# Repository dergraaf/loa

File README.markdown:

Project Loa
===========

The goal of the project is to develop a powerfull and flexible control board
for robotic (and other) applications.

A microcontroller from the STM32F series from ST is used as the central
processing unit. It is coupled with a Spartan-3 FPGA from Xilinx which will
be used as a powerfull I/O-Expander. With this combination it is possible to
control multiple motors with encoders and other actuators while processing
sensor data and controlling the robot.

For small robots everything will fit into the control board, for big system
the board can act as combined motor controller and sensor preprocessor.
The actual planning etc. can than be outsourced to a faster microcontroller
or PC connected via USB or a fast UART bus.

Naming
------

A "Loa" is a allknowing ghost in Voodoo. The different boards are named
after loas.

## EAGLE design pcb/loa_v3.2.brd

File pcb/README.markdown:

Documentation
=============

Microcontroller selection
-------------------------

For this controller board we wanted to use a Cortex-M3 chip. There are only two
families in wider use at the moment. The STM32F series from ST and the LPC1700
series from NXP.
One goal was that the microcontroller should be be able to control the drive
system of a robot without the FPGA. Therefore it needs to be able to read
four quadrature encoder and control two motors. This leaves only the STM32
series as the LPC1700 features only one quadrature encoder.

Currently there are four different strains within the STM32 series available.
The STM32F103 was the first one. A lot of development boards use controllers
from this series. But it has a quite long and annoying Errata Sheet, some
peripherals don't work with each other. Most important it is not possible to
use CAN and USB at the same time because they share an internal buffer.
After the 103er the 105/107er arrived. Their most important feature is that it
is possible to use CAN and USB at the same time. Some other stuff like the
ethernet interface are not important for us. The peripherals are improved,
leading to a shorter Errata Sheet. Their only drawback comparted to the 103er
series is that they are limited to 256kB Flash compared to a maximum of
1024kB for the 103er. The 256kB Flash might just be to few for the desired
application as a robot controller.

In the last time two new strains appeared. The STM32F200- and the
STM32F400-series. They are improvments of the 105/107er with a slightly
different pinout. Some of the power pins need to be connected differently, all
of the IO-Pins remain the same. Therefore it is possible to create a board
which supports STM32F1xx and STM32F2xx through some solder jumpers.
The STM32F207 are a bit faster (120MHz instead of 72MHz) and provide more Flash
memory (up to 1024kB). The STM32F407 uses an Cortex-M4 instead of the Cortex-M3
of all the other devices. With 150MHz and an integrated FPU it should be again
faster, especially for floating point calculations. The STM32F4xx are pin
compatible to the STM32F2xx.

As the STM32F4xx are to new and are not yet available from distributors like
Farnell we choose the STM32F207. This leaves the options of an upgrade to a
STM32F407 later.

STM32F207
---------

Pin  | Alternate Functions      | Usage on the Board         | Proposed Usage
---- | ------------------------ | -------------------------- | ----------------
PA0  | ADC0/Timer 2.1/Timer 5.1 |                            | Encoder 1
PA1  | ADC1/Timer 2.2/Timer 5.2 |                            | Encoder 1
PA2  | ADC2/Timer 9.1           |                            |     - 
PA3  | ADC3/Timer 9.2           |                            |     - 
PA4  | SPI1 Cs                  | -> FPGA (DIN)              | 
PA5  | SPI1 Sck                 | -> FPGA                    | 
PA6  | SPI1 Miso                | <- FPGA                    | 
PA7  | SPI1 Mosi                | -> FPGA                    | 
PA8  |                          | <- FPGA                    | 
PA9  | USB Vbus                 | <- USB                     | 
PA10 | USB ID                   | <- USB                     | 
PA11 | USB DM                   | <> USB                     | 
PA12 | USB DP                   | <> USB                     | 
PA13 | TMS                      | <- JTAG                    | 
PA14 | TCK                      | <- JTAG                    | 
PA15 | TDI                      | <- JTAG                    | 
---- | ------------------------ | -------------------------- | ----------------
PB0  | ADC8/Timer 3.3           |                            |     - 
PB1  | ADC9/Timer 3.4           |                            |     - 
PB2  | (BOOT1)                  | FPGA_CCLK                  | 
PB3  | TDO                      | -> JTAG                    | 
PB4  | Timer 3.1/TRST           |                            | Encoder 2
PB5  | Timer 3.2                |                            | Encoder 2
PB6  | UART1 Tx                 |                            | -> Upstream
PB7  | UART1 Rx                 |                            | <- Upstream
PB8  | I2C1 Scl                 |                            |     - 
PB9  | I2C1 Sda                 |                            |     - 
PB10 | I2C2 Scl                 |                            |     - 
PB11 | I2C2 Sda                 |                            |     - 
PB12 | SPI2 Cs /CAN2 Rx         |                            |     - 
PB13 | SPI2 Sck/CAN2 Tx         |                            |     - 
PB14 | SPI2 Miso                |                            |     - 
PB15 | SPI2 Mosi                |                            |     - 
---- | ------------------------ | -------------------------- | ----------------
PC0  | ADC10                    |                            |     - 
PC1  | ADC11                    |                            |     - 
PC2  | ADC12                    |                            |     - 
PC3  | ADC13                    |                            |     - 
PC4  | ADC14                    |                            |     - 
PC5  | ADC15                    |                            |     - 
PC6  | Timer 3.1/Timer 8.1      |                            | Encoder 3
PC7  | Timer 3.2/Timer 8.2      |                            | Encoder 3
PC8  | Timer 3.3/Timer 8.3      |                            |     - 
PC9  | Timer 3.4/Timer 8.4      |                            |     - 
PC10 | UART4 Tx                 |                            | SAB (Sensor Actor Bus)
PC11 | UART4 Rx                 |                            | SAB (       "        )
PC12 | UART5 Tx                 |                            | -> Debug UART
PC13 | (nur als Eingang)        | <- Button 1                | 
PC14 | (nur als Eingang)        | <- FPGA (DONE)             | 
PC15 | (nur als Eingang)        | <- SD Card Detect          | 
---- | ------------------------ | -------------------------- | ----------------
PD0  | CAN1 Rx                  | <- CAN                     | 
PD1  | CAN1 Tx                  | -> CAN                     | 
PD2  | UART5 Rx                 |                            | <- Debug UART
PD3  |                          | -> SD Card (CS)            | 
PD4  |                          |                            |     - 
PD5  | UART2 Tx                 |                            | SPI 1
PD6  | UART2 Rx                 |                            | SPI 1
PD7  | UART2 Ck                 |                            | SPI 1
PD8  | UART3 Tx                 | -> SD Card/Dataflash       | 
PD9  | UART3 Rx                 | <- SD Card/Dataflash       | 
PD10 | UART3 Ck                 | -> SD Card/Dataflash       | 
PD11 |                          | -> Dataflash (CS)          | 
PD12 | Timer 4.1                |                            | Encoder 4
PD13 | Timer 4.2                |                            | Encoder 4
PD14 | Timer 4.3                |                            |     - 
PD15 | Timer 4.4                |                            |     - 
---- | ------------------------ | -------------------------- | ----------------
PE0  |                          | -> FPGA (CCLK)             | 
PE1  |                          | -> FPGA (PROG_B)           | 
PE2  |                          | -> FPGA                    | 
PE3  |                          | -> LED0                    | 
PE4  |                          | -> LED1                    | 
PE5  | Timer 9.1                | -> LED2                    | 
PE6  | Timer 9.2                | -> LED3                    | 
PE7  |                          | <- FPGA (INIT_B)           | 
PE8  | Timer 1.1N               |                            | Motor 1
PE9  | Timer 1.1                |                            | Motor 1
PE10 | Timer 1.2N               |                            | Motor 2
PE11 | Timer 1.2                |                            | Motor 2
PE12 | Timer 1.3N               |                            |     - 
PE13 | Timer 1.3                |                            |     - 
PE14 | Timer 1.4                |                            |     - 
PE15 |                          |                            |     - 

#### Peripherals

- 2x Motor (Timer 1)
- 4x Encoder (Timer 3+4+5+8)

- 1x Upstream (Uart 1)
- 1x Debug (Uart 5)
- 2x SPI (Uart2+SPI2)
- 1x Peripheral UART (Uart 4)

#### SPI vs. SDIO

We choose a SPI over the SDIO interface for the SD Card because SDIO would
have blocked UART4 and UART5.

#### JTAG Connector

This is the official JTAG Connector proposed by ARM for the Cortex-M3. The only
difference is that we don't use a 1.27mm grid but a normal 2.54mm one. This
allows to use standard ribbon cable.

            ------
    3.3V --| 1  2 |-- TMS
     GND --| 3  4 |-- TCLK
     GND -[| 5  6 |-- TDO
    RTCK --| 7  8 |-- TDI
     GND --| 9 10 |-- Reset (SRST)
            ------

On this connector TRST (also called NJTRST) is not connected. This might
lead to the problem that the "reset halt" command from OpenOCD doesn't work.

RTCK is only used for ARM7 devices, so it is left open here.

FPGA Spartan-3
--------------

The Spartan-3 was choosen because it was the only FPGA from all the Spartan-3
Series (3,3E,3A,3AN) that is available in TQFP144 package from Reichelt or
Farnell.

The XC3S50A and XC3S50AN are also available, but the bigger packages are not.

### Pins

Unused pins are defined as inputs with pull-downs by default. Can be changed
by primitives or constraints in the bitstream generation.

All user-I/O pins, input-only pins, and dual-purpose pins that are not actively
involved in the currently-selected configuration mode are high impedance
(floating, three-stated, Hi-Z) during the configuration process.

### Configuration of the FPGA

DONE
:   Output with 2,5V supply. Driven low during configuration. Goes high after
    configuration has finished.

PROG_B
:   Input with 2,5 supply. Low pulse (>= 500ns) restarts the configuration
    process.

CCLK
:   Input with 2,5 supply in slave modes. Configuration clock.

DIN
:   Serial Mode input

DOUT
:   Serial Data Output. Not used in single FPGA designs.

INIT_B
:   Output with 3,3V supply. Driven low during before configuration. After it
    goes high the M[2:0] pins are sampled and the configuration is started.
    Holding the pin low stalls the configuration start. During configuration
    the FPGA indicates the occurrence of a configuration
    data error (i.e., CRC error) by asserting INIT_B Low.
    After configuration successfully completes, i.e., when the DONE pin goes
    High, the INIT_B pin is available as a full user-I/O pin.

HSWAP_EN 
:   When the pin is Low, each pin (not only the configuration pins) has an
    internal pull-up resistor that is active throughout configuration, starting
    immediately on power-up.

M[2:0]
:   Select the configuration mode.
    '111' Slave Serial Mode
    '101' JTAG Mode

#### Spartan 3 Bitstream Size

Device  | Configuration
        |  Size [Bits]
------- | --------------
XC3S50  |     439,264
XC3S200 |   1,047,616
XC3S400 |   1,699,136

### Power Supply

http://focus.ti.com/analog/docs/refdesignovw.tsp?familyId=64&contentType=2&genContentId=34823

For the XC3S250E:
- 1.2V at 1A
- 2.5V at 0.15A
- 3.3V at 3A

For the XC3S500E
- 1.2V at 1.5A
- 2.5V at 0.15A
- 3.3V at 3A

The XC3S200/400 should be somewhere in between, the XC3S50 significantly lower.

### JTAG Connector

The JTAG connector is a stripped down version of the original connector from
the Xilinx Parallel Cable IV. Original it uses 14 pins, but we leave the last
four pins out to fit it to a standard 10 pin header. These pins are only used
for programming the FPGA via Slave Serial mode through the PC so no
functionality is lost.

           ------
    GND --| 1  2 |-- Vref (connect to Vaux)
    GND --| 3  4 |-- TMS
    GND -[| 5  6 |-- TCK
    GND --| 7  8 |-- TDO
    GND --| 9 10 |-- TDI
           ------

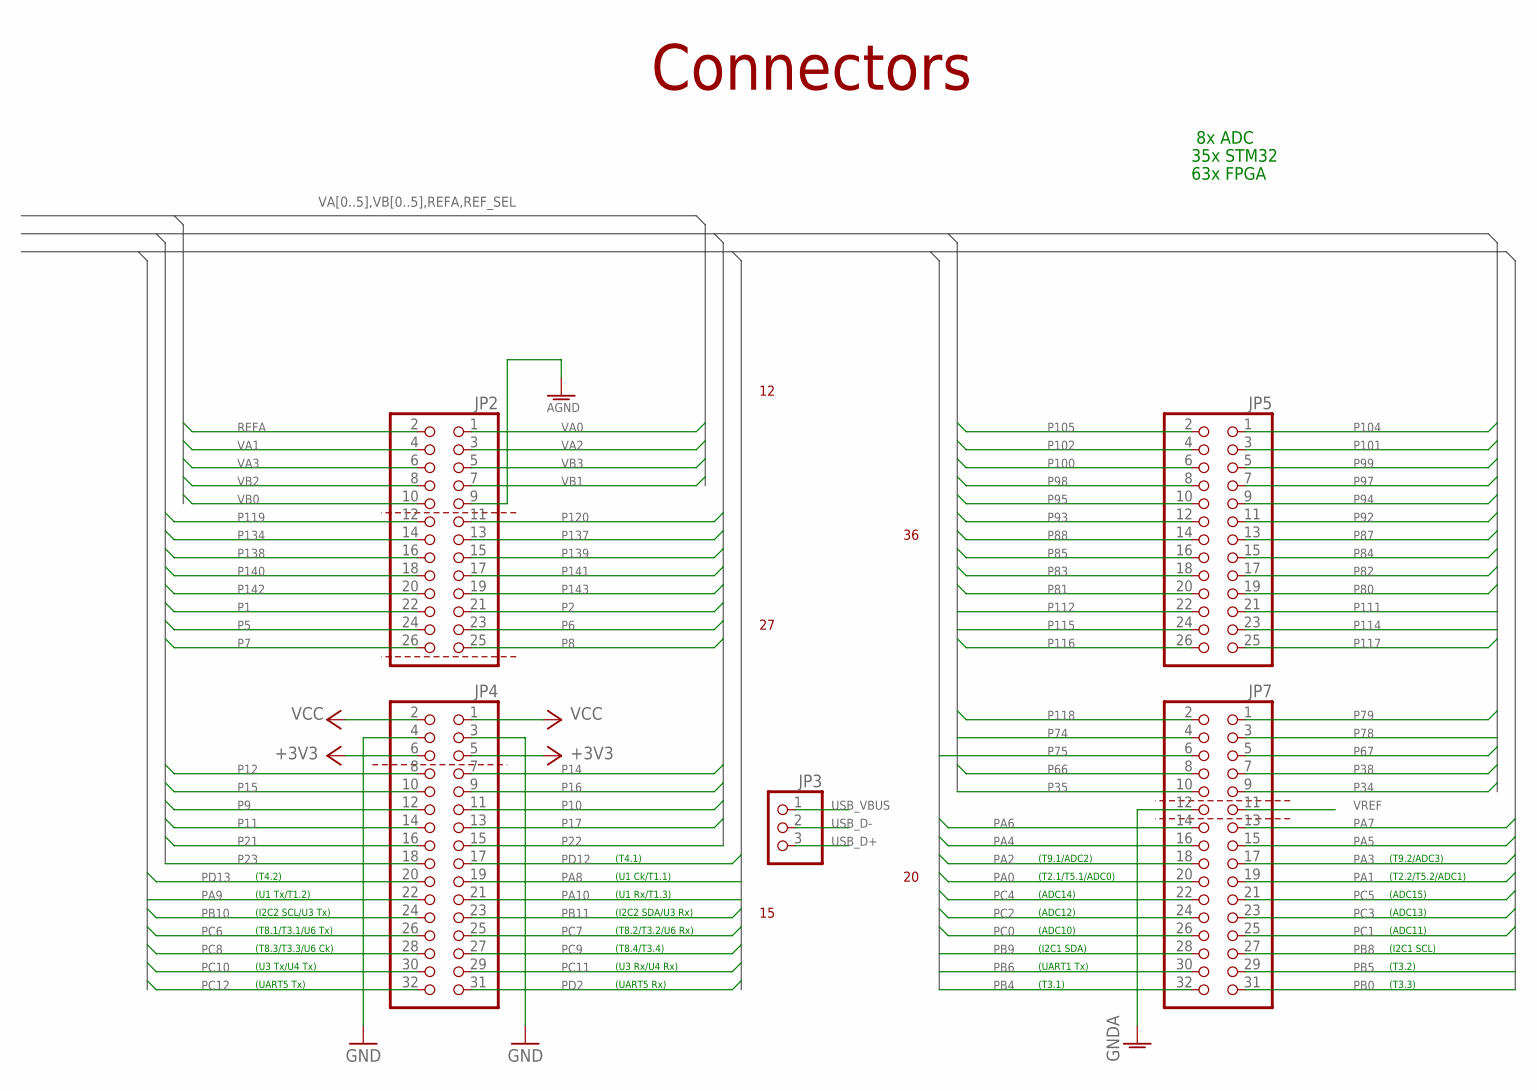
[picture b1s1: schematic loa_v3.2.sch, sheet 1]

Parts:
JP2, JP5: PINHD-2X13_2.54-SMD; 2X13SMD
JP3: PINHD-1X3_2.54S; 1X03S
JP4, JP7: PINHD-2X16_2.54-SMD; 2X16SMD

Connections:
+3V3: JP4.5, JP4.6; also elsewhere on the board
AGND: JP2.9; also elsewhere on the board
GND: JP4.3, JP4.4; also elsewhere on the board
GNDA: JP7.12; also elsewhere on the board
P1: JP2.22; also elsewhere on the board
P2: JP2.21; also elsewhere on the board
P5: JP2.24; also elsewhere on the board
P6: JP2.23; also elsewhere on the board
P7: JP2.26; also elsewhere on the board
P8: JP2.25; also elsewhere on the board
P9: JP4.12; also elsewhere on the board
P10: JP4.11; also elsewhere on the board
P11: JP4.14; also elsewhere on the board
P12: JP4.8; also elsewhere on the board
P14: JP4.7; also elsewhere on the board
P15: JP4.10; also elsewhere on the board
P16: JP4.9; also elsewhere on the board
P17: JP4.13; also elsewhere on the board
P21: JP4.16; also elsewhere on the board
P22: JP4.15; also elsewhere on the board
P23: JP4.18; also elsewhere on the board
P34: JP7.9; also elsewhere on the board
P35: JP7.10; also elsewhere on the board
P38: JP7.7; also elsewhere on the board
P66: JP7.8; also elsewhere on the board
P67: JP7.5; also elsewhere on the board
P74: JP7.4; also elsewhere on the board
P75: JP7.6; also elsewhere on the board
P78: JP7.3; also elsewhere on the board
P79: JP7.1; also elsewhere on the board
P80: JP5.19; also elsewhere on the board
P81: JP5.20; also elsewhere on the board
P82: JP5.17; also elsewhere on the board
P83: JP5.18; also elsewhere on the board
P84: JP5.15; also elsewhere on the board
P85: JP5.16; also elsewhere on the board
P87: JP5.13; also elsewhere on the board
P88: JP5.14; also elsewhere on the board
P92: JP5.11; also elsewhere on the board
P93: JP5.12; also elsewhere on the board
P94: JP5.9; also elsewhere on the board
P95: JP5.10; also elsewhere on the board
P97: JP5.7; also elsewhere on the board
P98: JP5.8; also elsewhere on the board
P99: JP5.5; also elsewhere on the board
P100: JP5.6; also elsewhere on the board
P101: JP5.3; also elsewhere on the board
P102: JP5.4; also elsewhere on the board
P104: JP5.1; also elsewhere on the board
P105: JP5.2; also elsewhere on the board
P111: JP5.21; also elsewhere on the board
P112: JP5.22; also elsewhere on the board
P114: JP5.23; also elsewhere on the board
P115: JP5.24; also elsewhere on the board
P116: JP5.26; also elsewhere on the board
P117: JP5.25; also elsewhere on the board
P118: JP7.2; also elsewhere on the board
P119: JP2.12; also elsewhere on the board
P120: JP2.11; also elsewhere on the board
P134: JP2.14; also elsewhere on the board
P137: JP2.13; also elsewhere on the board
P138: JP2.16; also elsewhere on the board
P139: JP2.15; also elsewhere on the board
P140: JP2.18; also elsewhere on the board
P141: JP2.17; also elsewhere on the board
P142: JP2.20; also elsewhere on the board
P143: JP2.19; also elsewhere on the board
PA0: JP7.20; also elsewhere on the board
PA1: JP7.19; also elsewhere on the board
PA2: JP7.18; also elsewhere on the board
PA3: JP7.17; also elsewhere on the board
PA4: JP7.16; also elsewhere on the board
PA5: JP7.15; also elsewhere on the board
PA6: JP7.14; also elsewhere on the board
PA7: JP7.13; also elsewhere on the board
PA8: JP4.19; also elsewhere on the board
PA9: JP4.22; also elsewhere on the board
PA10: JP4.21; also elsewhere on the board
PB0: JP7.31; also elsewhere on the board
PB4: JP7.32; also elsewhere on the board
PB5: JP7.29; also elsewhere on the board
PB6: JP7.30; also elsewhere on the board
PB8: JP7.27; also elsewhere on the board
PB9: JP7.28; also elsewhere on the board
PB10: JP4.24; also elsewhere on the board
PB11: JP4.23; also elsewhere on the board
PC0: JP7.26; also elsewhere on the board
PC1: JP7.25; also elsewhere on the board
PC2: JP7.24; also elsewhere on the board
PC3: JP7.23; also elsewhere on the board
PC4: JP7.22; also elsewhere on the board
PC5: JP7.21; also elsewhere on the board
PC6: JP4.26; also elsewhere on the board
PC7: JP4.25; also elsewhere on the board
PC8: JP4.28; also elsewhere on the board
PC9: JP4.27; also elsewhere on the board
PC10: JP4.30; also elsewhere on the board
PC11: JP4.29; also elsewhere on the board
PC12: JP4.32; also elsewhere on the board
PD2: JP4.31; also elsewhere on the board
PD12: JP4.17; also elsewhere on the board
PD13: JP4.20; also elsewhere on the board
REFA: JP2.2; also elsewhere on the board
USB_D+: JP3.3; also elsewhere on the board
USB_D-: JP3.2; also elsewhere on the board
USB_VBUS: JP3.1; also elsewhere on the board
VA0: JP2.1; also elsewhere on the board
VA1: JP2.4; also elsewhere on the board
VA2: JP2.3; also elsewhere on the board
VA3: JP2.6; also elsewhere on the board
VB0: JP2.10; also elsewhere on the board
VB1: JP2.7; also elsewhere on the board
VB2: JP2.8; also elsewhere on the board
VB3: JP2.5; also elsewhere on the board
VCC: JP4.1, JP4.2; also elsewhere on the board
VREF: JP7.11; also elsewhere on the board

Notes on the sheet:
Connectors
(T2.1/T5.1/ADC0)
(T2.2/T5.2/ADC1)
(T9.1/ADC2)
(T9.2/ADC3)
(ADC10)
(ADC11)
(ADC12)
(ADC13)
(ADC14)
(ADC15)
(I2C1 SCL)
(I2C1 SDA)
(UART1 Tx)
(T3.1)
(T3.2)
(UART5 Rx)
(UART5 Tx)
(T8.1/T3.1/U6 Tx)
(T8.2/T3.2/U6 Rx)
(T8.3/T3.3/U6 Ck)
(T8.4/T3.4)
(T4.2)
(T4.1)
(U1 Tx/T1.2)
(U1 Rx/T1.3)
(U1 Ck/T1.1)
(U3 Tx/U4 Tx)
(U3 Rx/U4 Rx)
(I2C2 SDA/U3 Rx)
(I2C2 SCL/U3 Tx)
8x ADC
35x STM32
63x FPGA
(T3.3)

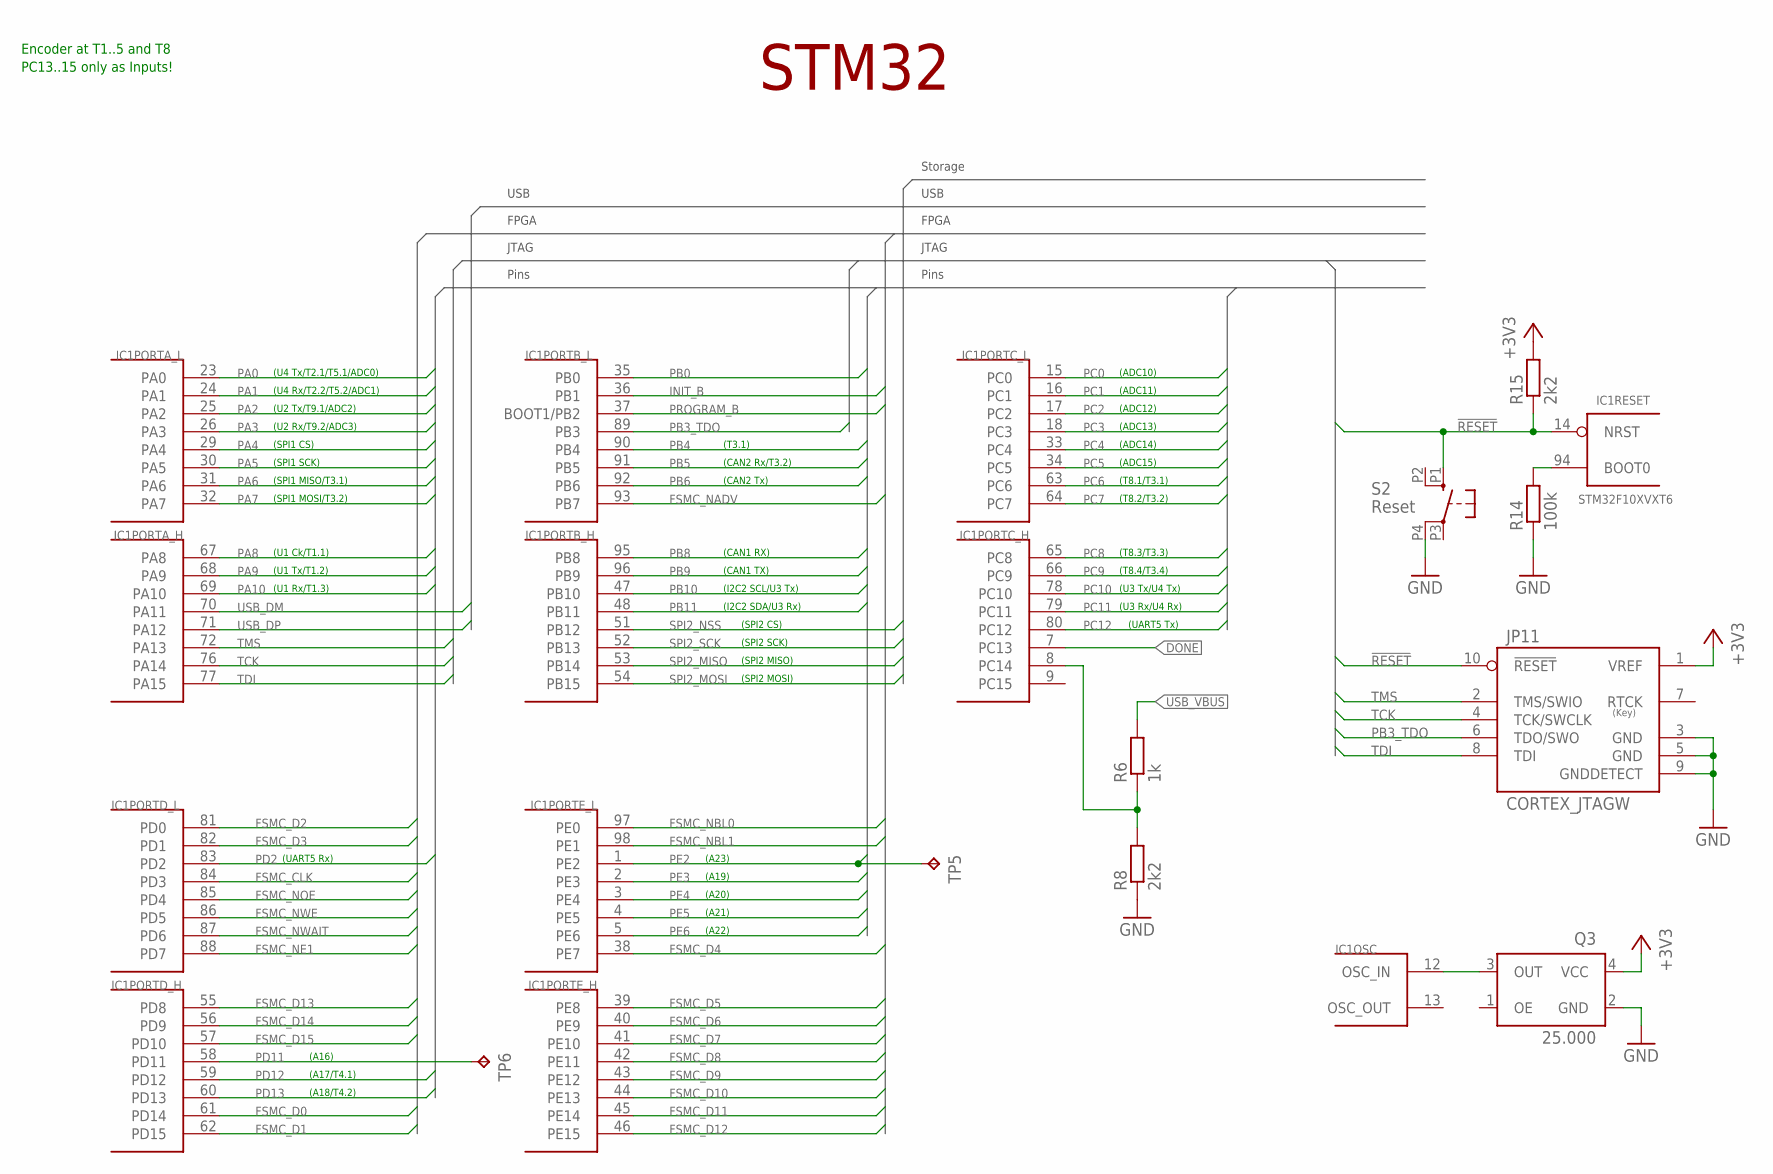
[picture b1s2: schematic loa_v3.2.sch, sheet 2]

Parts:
IC1: STM32F10XVXT6; TQFP100; DIGIKEY# 497-11605-ND
JP11: CORTEX_JTAGW; ML10
Q3: 25.000; XO53
R6: 1k; R0603
R8, R15: 2k2; R0603
R14: 100k; R0603
S2: Reset; B3F-10XX-SMD
TP5, TP6: TPB1,27; B1,27

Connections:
!RESET: IC1.14 (NRST), JP11.10 (!RESET), R15.1, S2.P1 (S)
+3V3: JP11.1 (VREF), Q3.4 (VCC), R15.2; also elsewhere on the board
DONE: IC1.7 (PC13); also elsewhere on the board
FSMC_CLK: IC1.84 (PD3); also elsewhere on the board
FSMC_D0: IC1.61 (PD14); also elsewhere on the board
FSMC_D1: IC1.62 (PD15); also elsewhere on the board
FSMC_D2: IC1.81 (PD0); also elsewhere on the board
FSMC_D3: IC1.82 (PD1); also elsewhere on the board
FSMC_D4: IC1.38 (PE7); also elsewhere on the board
FSMC_D5: IC1.39 (PE8); also elsewhere on the board
FSMC_D6: IC1.40 (PE9); also elsewhere on the board
FSMC_D7: IC1.41 (PE10); also elsewhere on the board
FSMC_D8: IC1.42 (PE11); also elsewhere on the board
FSMC_D9: IC1.43 (PE12); also elsewhere on the board
FSMC_D10: IC1.44 (PE13); also elsewhere on the board
FSMC_D11: IC1.45 (PE14); also elsewhere on the board
FSMC_D12: IC1.46 (PE15); also elsewhere on the board
FSMC_D13: IC1.55 (PD8); also elsewhere on the board
FSMC_D14: IC1.56 (PD9); also elsewhere on the board
FSMC_D15: IC1.57 (PD10); also elsewhere on the board
FSMC_NADV: IC1.93 (PB7); also elsewhere on the board
FSMC_NBL0: IC1.97 (PE0); also elsewhere on the board
FSMC_NBL1: IC1.98 (PE1); also elsewhere on the board
FSMC_NE1: IC1.88 (PD7); also elsewhere on the board
FSMC_NOE: IC1.85 (PD4); also elsewhere on the board
FSMC_NWAIT: IC1.87 (PD6); also elsewhere on the board
FSMC_NWE: IC1.86 (PD5); also elsewhere on the board
GND: JP11.3 (GND), JP11.5 (GND), JP11.9 (GNDDETECT), Q3.2 (GND), R8.1, R14.1, S2.P4 (P1); also elsewhere on the board
INIT_B: IC1.36 (PB1); also elsewhere on the board
unnamed: IC1.8 (PC14), R6.1, R8.2
unnamed: IC1.94 (BOOT0), R14.2
unnamed: IC1.12 (OSC_IN), Q3.3 (OUT)
PA0: IC1.23 (PA0); also elsewhere on the board
PA1: IC1.24 (PA1); also elsewhere on the board
PA2: IC1.25 (PA2); also elsewhere on the board
PA3: IC1.26 (PA3); also elsewhere on the board
PA4: IC1.29 (PA4); also elsewhere on the board
PA5: IC1.30 (PA5); also elsewhere on the board
PA6: IC1.31 (PA6); also elsewhere on the board
PA7: IC1.32 (PA7); also elsewhere on the board
PA8: IC1.67 (PA8); also elsewhere on the board
PA9: IC1.68 (PA9); also elsewhere on the board
PA10: IC1.69 (PA10); also elsewhere on the board
PB0: IC1.35 (PB0); also elsewhere on the board
PB3_TDO: IC1.89 (PB3), JP11.6 (TDO/SWO)
PB4: IC1.90 (PB4); also elsewhere on the board
PB5: IC1.91 (PB5); also elsewhere on the board
PB6: IC1.92 (PB6); also elsewhere on the board
PB8: IC1.95 (PB8); also elsewhere on the board
PB9: IC1.96 (PB9); also elsewhere on the board
PB10: IC1.47 (PB10); also elsewhere on the board
PB11: IC1.48 (PB11); also elsewhere on the board
PC0: IC1.15 (PC0); also elsewhere on the board
PC1: IC1.16 (PC1); also elsewhere on the board
PC2: IC1.17 (PC2); also elsewhere on the board
PC3: IC1.18 (PC3); also elsewhere on the board
PC4: IC1.33 (PC4); also elsewhere on the board
PC5: IC1.34 (PC5); also elsewhere on the board
PC6: IC1.63 (PC6); also elsewhere on the board
PC7: IC1.64 (PC7); also elsewhere on the board
PC8: IC1.65 (PC8); also elsewhere on the board
PC9: IC1.66 (PC9); also elsewhere on the board
PC10: IC1.78 (PC10); also elsewhere on the board
PC11: IC1.79 (PC11); also elsewhere on the board
PC12: IC1.80 (PC12); also elsewhere on the board
PD2: IC1.83 (PD2); also elsewhere on the board
PD11: IC1.58 (PD11), TP6.TP
PD12: IC1.59 (PD12); also elsewhere on the board
PD13: IC1.60 (PD13); also elsewhere on the board
PE2: IC1.1 (PE2), TP5.TP
PE3: IC1.2 (PE3); also elsewhere on the board
PE4: IC1.3 (PE4); also elsewhere on the board
PE5: IC1.4 (PE5); also elsewhere on the board
PE6: IC1.5 (PE6); also elsewhere on the board
PROGRAM_B: IC1.37 (BOOT1/PB2); also elsewhere on the board
SPI2_MISO: IC1.53 (PB14); also elsewhere on the board
SPI2_MOSI: IC1.54 (PB15); also elsewhere on the board
SPI2_NSS: IC1.51 (PB12); also elsewhere on the board
SPI2_SCK: IC1.52 (PB13); also elsewhere on the board
TCK: IC1.76 (PA14), JP11.4 (TCK/SWCLK)
TDI: IC1.77 (PA15), JP11.8 (TDI)
TMS: IC1.72 (PA13), JP11.2 (TMS/SWIO)
USB_DM: IC1.70 (PA11); also elsewhere on the board
USB_DP: IC1.71 (PA12); also elsewhere on the board
USB_VBUS: R6.2; also elsewhere on the board

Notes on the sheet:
(U4 Tx/T2.1/T5.1/ADC0)
(U4 Rx/T2.2/T5.2/ADC1)
(U2 Tx/T9.1/ADC2)
(U2 Rx/T9.2/ADC3)
(T3.1)
(CAN2 Rx/T3.2)
(CAN1 RX)
(CAN1 TX)
(I2C2 SDA/U3 Rx)
(I2C2 SCL/U3 Tx)
(CAN2 Tx)
(U3 Tx/U4 Tx)
(U3 Rx/U4 Rx)
(UART5 Rx)
STM32
Encoder at T1..5 and T8
(ADC10)
(ADC11)
(ADC12)
(ADC13)
(ADC14)
(ADC15)
(T8.1/T3.1)
(T8.2/T3.2)
(T8.3/T3.3)
(T8.4/T3.4)
PC13..15 only as Inputs!
(UART5 Tx)
(A18/T4.2)
(A17/T4.1)
(A16)
(A23)
(A19)
(A20)
(A21)
(A22)
(U1 Tx/T1.2)
(U1 Rx/T1.3)
(SPI1 CS)
(SPI1 SCK)

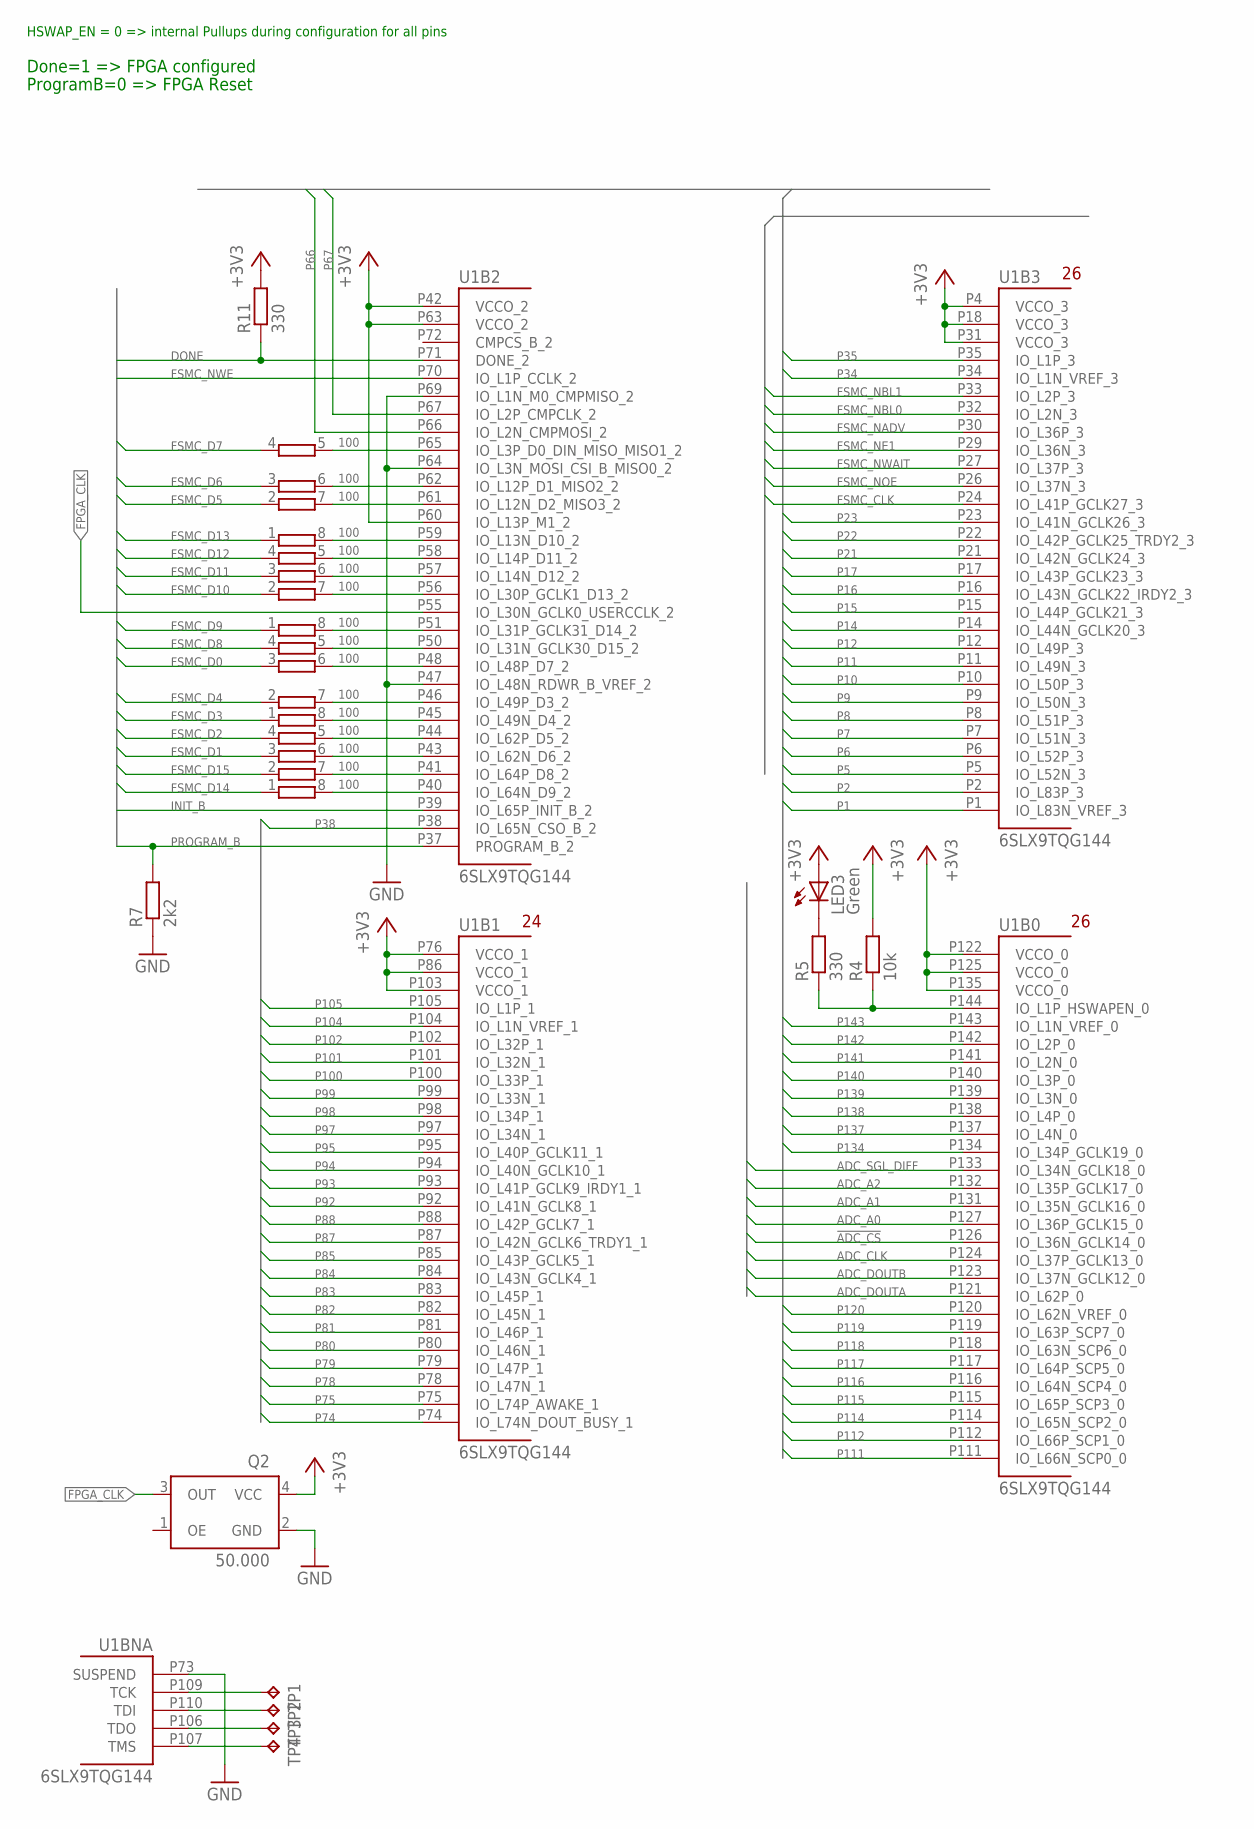
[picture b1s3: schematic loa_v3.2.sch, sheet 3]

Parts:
LED3: Green; CHIPLED_0805
Q2: 50.000; XO53
R4: 10k; R0603
R5, R11: 330; R0603
R7: 2k2; R0805
RN3, RN4, RN6, RN7: 100; EXB38V
TP1, TP2, TP3, TP4: TPB1,27; B1,27
U1: 6SLX9TQG144; TQ144; DIGIKEY# 122-1745-ND

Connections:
!ADC_CS: U1.P126 (IO_L36N_GCLK14_0); also elsewhere on the board
+3V3: LED3.A, Q2.4 (VCC), R4.2, R11.2, U1.P4 (VCCO_3), U1.P18 (VCCO_3), U1.P31 (VCCO_3), U1.P42 (VCCO_2), U1.P60 (IO_L13P_M1_2), U1.P63 (VCCO_2), U1.P76 (VCCO_1), U1.P86 (VCCO_1), U1.P103 (VCCO_1), U1.P122 (VCCO_0), U1.P125 (VCCO_0), U1.P135 (VCCO_0); also elsewhere on the board
ADC_A0: U1.P127 (IO_L36P_GCLK15_0); also elsewhere on the board
ADC_A1: U1.P131 (IO_L35N_GCLK16_0); also elsewhere on the board
ADC_A2: U1.P132 (IO_L35P_GCLK17_0); also elsewhere on the board
ADC_CLK: U1.P124 (IO_L37P_GCLK13_0); also elsewhere on the board
ADC_DOUTA: U1.P121 (IO_L62P_0); also elsewhere on the board
ADC_DOUTB: U1.P123 (IO_L37N_GCLK12_0); also elsewhere on the board
ADC_SGL_DIFF: U1.P133 (IO_L34N_GCLK18_0); also elsewhere on the board
DONE: R11.1, U1.P71 (DONE_2); also elsewhere on the board
FPGA_CLK: Q2.3 (OUT), U1.P55 (IO_L30N_GCLK0_USERCCLK_2)
FPGA_TCK: TP1.TP, U1.P109 (TCK)
FPGA_TDI: TP2.TP, U1.P110 (TDI)
FPGA_TDO: TP3.TP, U1.P106 (TDO)
FPGA_TMS: TP4.TP, U1.P107 (TMS)
FSMC_CLK: U1.P24 (IO_L41P_GCLK27_3); also elsewhere on the board
FSMC_D0: RN7.3 (1); also elsewhere on the board
FSMC_D1: RN4.3 (1); also elsewhere on the board
FSMC_D2: RN4.4 (1); also elsewhere on the board
FSMC_D3: RN7.1; also elsewhere on the board
FSMC_D4: RN7.2 (1); also elsewhere on the board
FSMC_D5: RN3.2 (1); also elsewhere on the board
FSMC_D6: RN3.3 (1); also elsewhere on the board
FSMC_D7: RN3.4 (1); also elsewhere on the board
FSMC_D8: RN7.4 (1); also elsewhere on the board
FSMC_D9: RN6.1; also elsewhere on the board
FSMC_D10: RN6.2 (1); also elsewhere on the board
FSMC_D11: RN6.3 (1); also elsewhere on the board
FSMC_D12: RN6.4 (1); also elsewhere on the board
FSMC_D13: RN3.1; also elsewhere on the board
FSMC_D14: RN4.1; also elsewhere on the board
FSMC_D15: RN4.2 (1); also elsewhere on the board
FSMC_NADV: U1.P30 (IO_L36P_3); also elsewhere on the board
FSMC_NBL0: U1.P32 (IO_L2N_3); also elsewhere on the board
FSMC_NBL1: U1.P33 (IO_L2P_3); also elsewhere on the board
FSMC_NE1: U1.P29 (IO_L36N_3); also elsewhere on the board
FSMC_NOE: U1.P26 (IO_L37N_3); also elsewhere on the board
FSMC_NWAIT: U1.P27 (IO_L37P_3); also elsewhere on the board
FSMC_NWE: U1.P70 (IO_L1P_CCLK_2); also elsewhere on the board
GND: Q2.2 (GND), R7.1, U1.P47 (IO_L48N_RDWR_B_VREF_2), U1.P64 (IO_L3N_MOSI_CSI_B_MISO0_2), U1.P69 (IO_L1N_M0_CMPMISO_2), U1.P73 (SUSPEND); also elsewhere on the board
INIT_B: U1.P39 (IO_L65P_INIT_B_2); also elsewhere on the board
unnamed: RN3.5 (2), U1.P65 (IO_L3P_D0_DIN_MISO_MISO1_2)
unnamed: RN3.6 (2), U1.P62 (IO_L12P_D1_MISO2_2)
unnamed: RN3.7 (2), U1.P61 (IO_L12N_D2_MISO3_2)
unnamed: RN3.8 (2), U1.P59 (IO_L13N_D10_2)
unnamed: RN6.5 (2), U1.P58 (IO_L14P_D11_2)
unnamed: RN6.6 (2), U1.P57 (IO_L14N_D12_2)
unnamed: RN6.7 (2), U1.P56 (IO_L30P_GCLK1_D13_2)
unnamed: RN6.8 (2), U1.P51 (IO_L31P_GCLK31_D14_2)
unnamed: RN7.5 (2), U1.P50 (IO_L31N_GCLK30_D15_2)
unnamed: RN7.6 (2), U1.P48 (IO_L48P_D7_2)
unnamed: RN7.7 (2), U1.P46 (IO_L49P_D3_2)
unnamed: RN7.8 (2), U1.P45 (IO_L49N_D4_2)
unnamed: RN4.5 (2), U1.P44 (IO_L62P_D5_2)
unnamed: LED3.C, R5.2
unnamed: R4.1, R5.1, U1.P144 (IO_L1P_HSWAPEN_0)
unnamed: RN4.7 (2), U1.P41 (IO_L64P_D8_2)
unnamed: RN4.6 (2), U1.P43 (IO_L62N_D6_2)
unnamed: RN4.8 (2), U1.P40 (IO_L64N_D9_2)
P1: U1.P1 (IO_L83N_VREF_3); also elsewhere on the board
P2: U1.P2 (IO_L83P_3); also elsewhere on the board
P5: U1.P5 (IO_L52N_3); also elsewhere on the board
P6: U1.P6 (IO_L52P_3); also elsewhere on the board
P7: U1.P7 (IO_L51N_3); also elsewhere on the board
P8: U1.P8 (IO_L51P_3); also elsewhere on the board
P9: U1.P9 (IO_L50N_3); also elsewhere on the board
P10: U1.P10 (IO_L50P_3); also elsewhere on the board
P11: U1.P11 (IO_L49N_3); also elsewhere on the board
P12: U1.P12 (IO_L49P_3); also elsewhere on the board
P14: U1.P14 (IO_L44N_GCLK20_3); also elsewhere on the board
P15: U1.P15 (IO_L44P_GCLK21_3); also elsewhere on the board
P16: U1.P16 (IO_L43N_GCLK22_IRDY2_3); also elsewhere on the board
P17: U1.P17 (IO_L43P_GCLK23_3); also elsewhere on the board
P21: U1.P21 (IO_L42N_GCLK24_3); also elsewhere on the board
P22: U1.P22 (IO_L42P_GCLK25_TRDY2_3); also elsewhere on the board
P23: U1.P23 (IO_L41N_GCLK26_3); also elsewhere on the board
P34: U1.P34 (IO_L1N_VREF_3); also elsewhere on the board
P35: U1.P35 (IO_L1P_3); also elsewhere on the board
P38: U1.P38 (IO_L65N_CSO_B_2); also elsewhere on the board
P66: U1.P66 (IO_L2N_CMPMOSI_2); also elsewhere on the board
P67: U1.P67 (IO_L2P_CMPCLK_2); also elsewhere on the board
P74: U1.P74 (IO_L74N_DOUT_BUSY_1); also elsewhere on the board
P75: U1.P75 (IO_L74P_AWAKE_1); also elsewhere on the board
P78: U1.P78 (IO_L47N_1); also elsewhere on the board
P79: U1.P79 (IO_L47P_1); also elsewhere on the board
P80: U1.P80 (IO_L46N_1); also elsewhere on the board
P81: U1.P81 (IO_L46P_1); also elsewhere on the board
P82: U1.P82 (IO_L45N_1); also elsewhere on the board
P83: U1.P83 (IO_L45P_1); also elsewhere on the board
P84: U1.P84 (IO_L43N_GCLK4_1); also elsewhere on the board
P85: U1.P85 (IO_L43P_GCLK5_1); also elsewhere on the board
P87: U1.P87 (IO_L42N_GCLK6_TRDY1_1); also elsewhere on the board
P88: U1.P88 (IO_L42P_GCLK7_1); also elsewhere on the board
P92: U1.P92 (IO_L41N_GCLK8_1); also elsewhere on the board
P93: U1.P93 (IO_L41P_GCLK9_IRDY1_1); also elsewhere on the board
P94: U1.P94 (IO_L40N_GCLK10_1); also elsewhere on the board
P95: U1.P95 (IO_L40P_GCLK11_1); also elsewhere on the board
P97: U1.P97 (IO_L34N_1); also elsewhere on the board
P98: U1.P98 (IO_L34P_1); also elsewhere on the board
P99: U1.P99 (IO_L33N_1); also elsewhere on the board
P100: U1.P100 (IO_L33P_1); also elsewhere on the board
P101: U1.P101 (IO_L32N_1); also elsewhere on the board
P102: U1.P102 (IO_L32P_1); also elsewhere on the board
P104: U1.P104 (IO_L1N_VREF_1); also elsewhere on the board
P105: U1.P105 (IO_L1P_1); also elsewhere on the board
P111: U1.P111 (IO_L66N_SCP0_0); also elsewhere on the board
P112: U1.P112 (IO_L66P_SCP1_0); also elsewhere on the board
P114: U1.P114 (IO_L65N_SCP2_0); also elsewhere on the board
P115: U1.P115 (IO_L65P_SCP3_0); also elsewhere on the board
P116: U1.P116 (IO_L64N_SCP4_0); also elsewhere on the board
P117: U1.P117 (IO_L64P_SCP5_0); also elsewhere on the board
P118: U1.P118 (IO_L63N_SCP6_0); also elsewhere on the board
P119: U1.P119 (IO_L63P_SCP7_0); also elsewhere on the board
P120: U1.P120 (IO_L62N_VREF_0); also elsewhere on the board
P134: U1.P134 (IO_L34P_GCLK19_0); also elsewhere on the board
P137: U1.P137 (IO_L4N_0); also elsewhere on the board
P138: U1.P138 (IO_L4P_0); also elsewhere on the board
P139: U1.P139 (IO_L3N_0); also elsewhere on the board
P140: U1.P140 (IO_L3P_0); also elsewhere on the board
P141: U1.P141 (IO_L2N_0); also elsewhere on the board
P142: U1.P142 (IO_L2P_0); also elsewhere on the board
P143: U1.P143 (IO_L1N_VREF_0); also elsewhere on the board
PROGRAM_B: R7.2, U1.P37 (PROGRAM_B_2); also elsewhere on the board

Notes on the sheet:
Done=1 => FPGA configured
ProgramB=0 => FPGA Reset
HSWAP_EN = 0 => internal Pullups during configuration for all pins

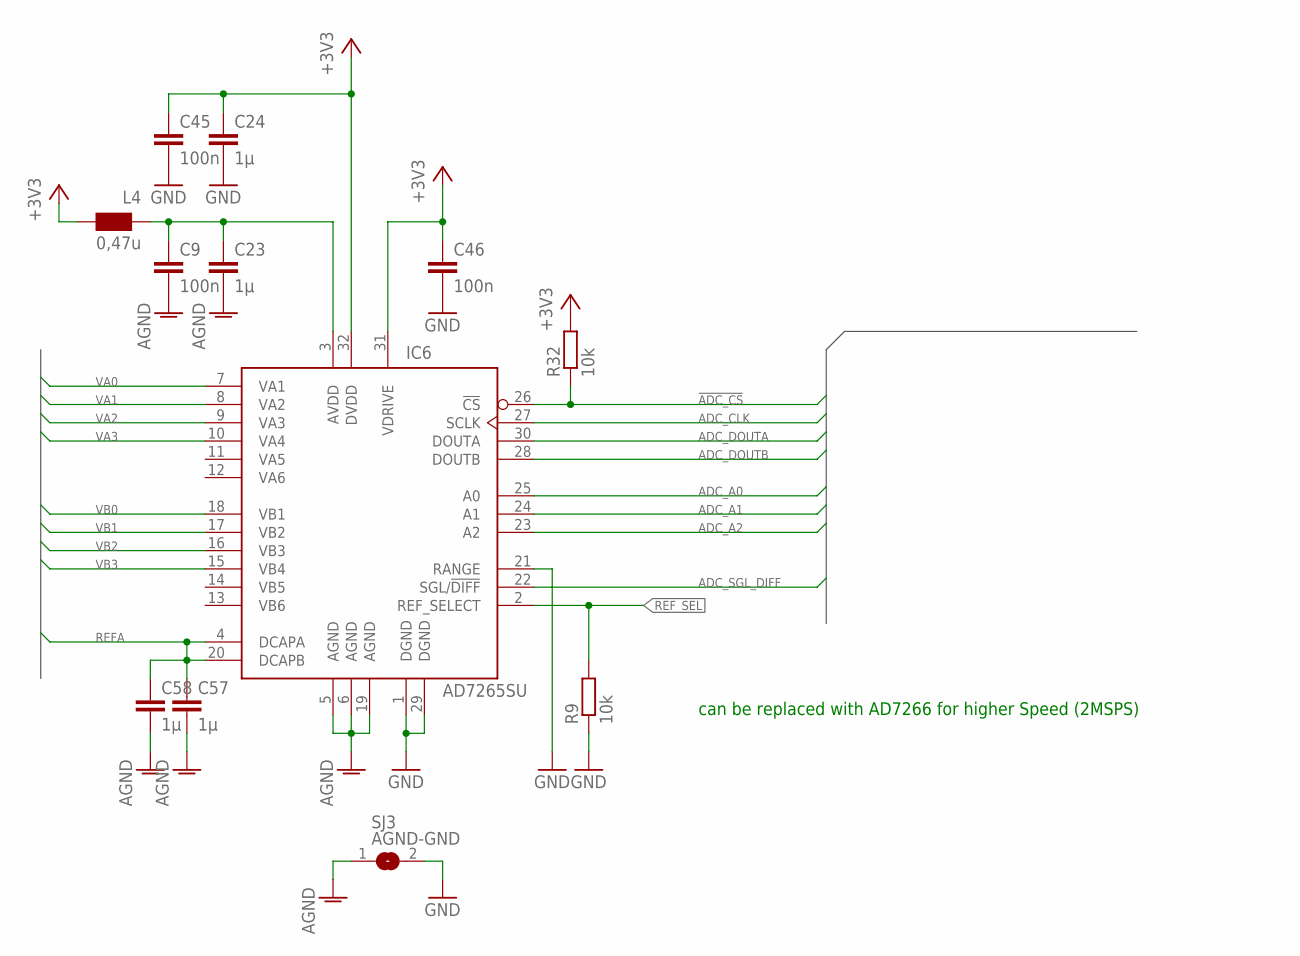
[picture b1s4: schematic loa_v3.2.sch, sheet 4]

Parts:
C9, C45, C46: 100n; C0603
C23, C24, C57, C58: 1µ; C0805
IC6: AD7265SU; TQFP32-08; DIGIKEY# AD7265BSUZ-ND
L4: 0,47u; WE-KI_0805_B
R9, R32: 10k; R0603
SJ3: AGND-GND; SJS

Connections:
!ADC_CS: IC6.26 (!CS), R32.1; also elsewhere on the board
+3V3: C24.1, C45.1, C46.1, IC6.31 (VDRIVE), IC6.32 (DVDD), L4.1 (2), R32.2; also elsewhere on the board
ADC_A0: IC6.25 (A0); also elsewhere on the board
ADC_A1: IC6.24 (A1); also elsewhere on the board
ADC_A2: IC6.23 (A2); also elsewhere on the board
ADC_CLK: IC6.27 (SCLK); also elsewhere on the board
ADC_DOUTA: IC6.30 (DOUTA); also elsewhere on the board
ADC_DOUTB: IC6.28 (DOUTB); also elsewhere on the board
ADC_SGL_DIFF: IC6.22 (SGL/!DIFF); also elsewhere on the board
AGND: C9.2, C23.2, C57.2, C58.2, IC6.5 (AGND), IC6.6 (AGND), IC6.19 (AGND), SJ3.1; also elsewhere on the board
GND: C24.2, C45.2, C46.2, IC6.1 (DGND), IC6.21 (RANGE), IC6.29 (DGND), R9.1, SJ3.2; also elsewhere on the board
unnamed: C9.1, C23.1, IC6.3 (AVDD), L4.2 (1)
REFA: C57.1, C58.1, IC6.4 (DCAPA), IC6.20 (DCAPB); also elsewhere on the board
REF_SEL: IC6.2 (REF_SELECT), R9.2
VA0: IC6.7 (VA1); also elsewhere on the board
VA1: IC6.8 (VA2); also elsewhere on the board
VA2: IC6.9 (VA3); also elsewhere on the board
VA3: IC6.10 (VA4); also elsewhere on the board
VB0: IC6.18 (VB1); also elsewhere on the board
VB1: IC6.17 (VB2); also elsewhere on the board
VB2: IC6.16 (VB3); also elsewhere on the board
VB3: IC6.15 (VB4); also elsewhere on the board

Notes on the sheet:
can be replaced with AD7266 for higher Speed (2MSPS)
